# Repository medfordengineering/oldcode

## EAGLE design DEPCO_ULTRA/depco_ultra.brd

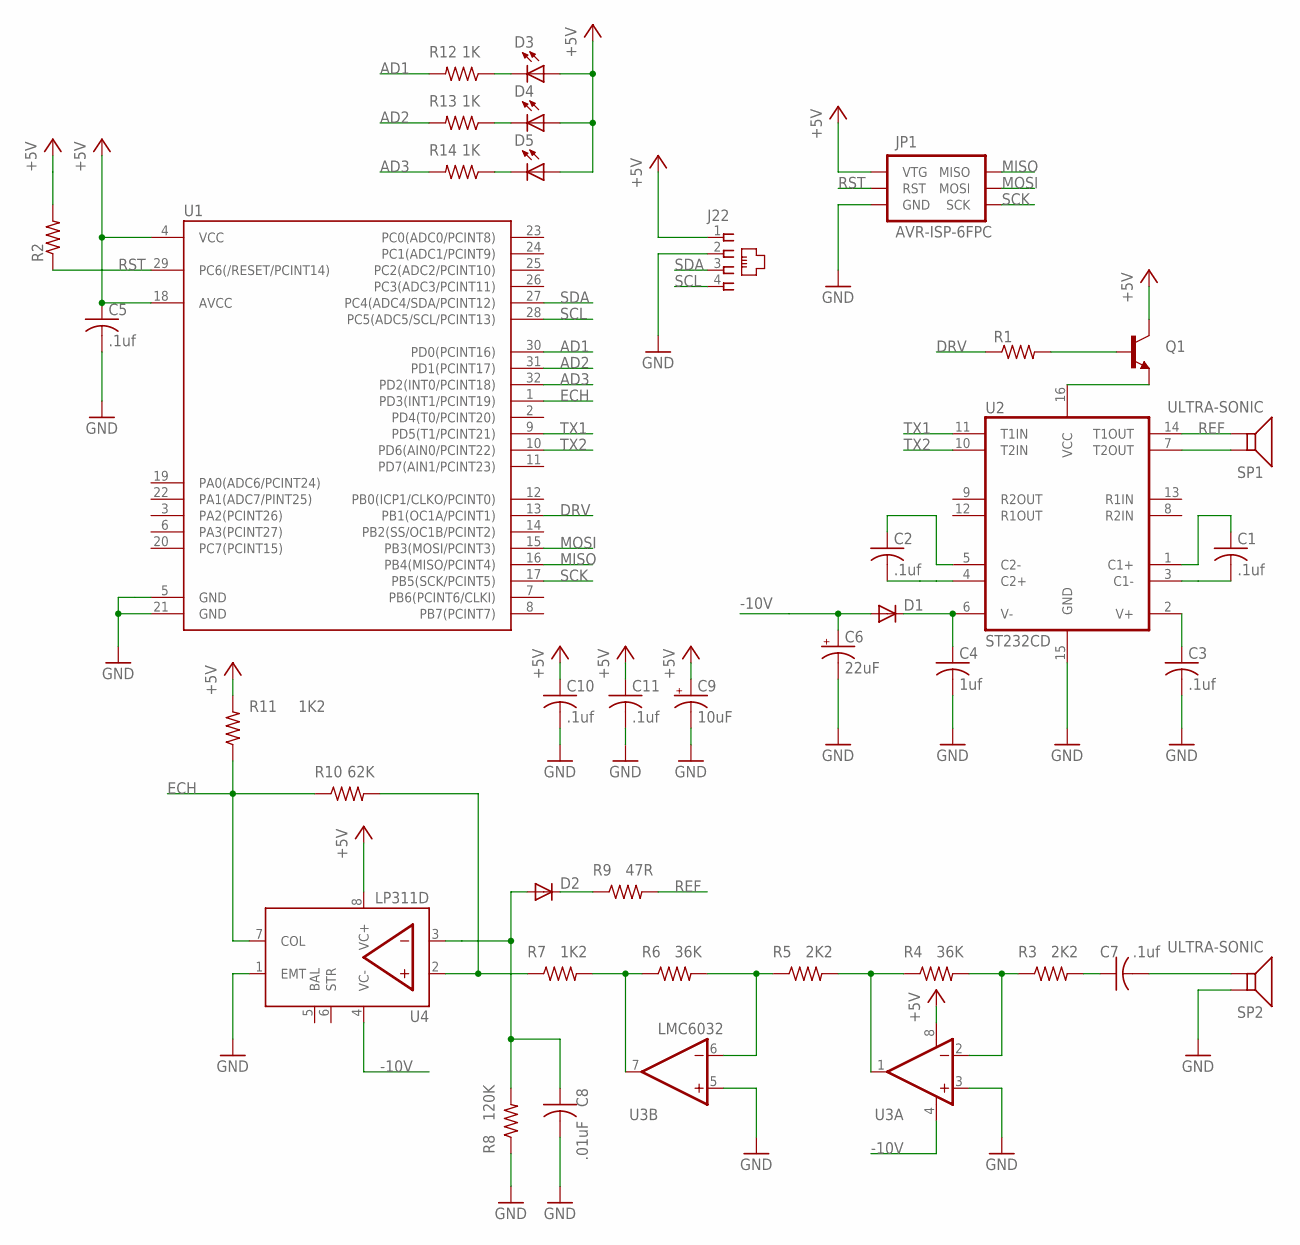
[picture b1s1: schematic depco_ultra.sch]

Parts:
C1, C2, C3, C5, C7, C10, C11: .1uf; C0805
C4: 1uf; C0805
C6: 22uF; PANASONIC_D
C8: .01uF; C0805
C9: 10uF; PANASONIC_D
D1, D2: DIODESOD; SOD-323
D3, D4, D5: LED_MS; LED-0805
J22: 555165-2
JP1: AVR-ISP-6FPC; 84981-6
Q1: TRANSISTOR_NPNSOT23; SOT23
R1, R2: R-US_M0805; M0805
R3, R5: 2K2; M0805
R4, R6: 36K; M0805
R7, R11: 1K2; M0805
R8: 120K; M0805
R9: 47R; M0805
R10: 62K; M0805
R12, R13, R14: 1K; M0805
SP1, SP2: ULTRA-SONIC; 400_D64INC
U1: ATTINY48-QFN; TQFP32-08
U2: ST232CD; SO016
U3: LMC6032; SO08
U4: LP311D; SO08

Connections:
+5V: C5.1, C9.+, C10.1, C11.1, D3.A, D4.A, D5.A, J22.1, JP1.5 (VTG), Q1.3 (C), R2.2, R11.2, U1.4 (VCC), U1.18 (AVCC), U3.8 (V+), U4.8 (VC+)
-10V: C6.+, D1.2 (A), U3.4 (V-), U4.4 (VC-)
AD1: R12.2, U1.30 (PD0(PCINT16))
AD2: R13.2, U1.31 (PD1(PCINT17))
AD3: R14.2, U1.32 (PD2(INT0/PCINT18))
DRV: R1.1, U1.13 (PB1(OC1A/PCINT1))
ECH: R10.1, R11.1, U1.1 (PD3(INT1/PCINT19)), U4.7 (COL)
GND: C3.2, C4.2, C5.2, C6.-, C8.2, C9.-, C10.2, C11.2, J22.2, JP1.6 (GND), R8.1, SP2.1 (P+), U1.5 (GND), U1.21 (GND), U2.15 (GND), U3.3 (+IN), U3.5 (+IN), U4.1 (EMT)
MISO: JP1.2 (MISO), U1.16 (PB4(MISO/PCINT4))
MOSI: JP1.3 (MOSI), U1.15 (PB3(MOSI/PCINT3))
unnamed: C2.1, U2.5 (C2-)
unnamed: C2.2, U2.4 (C2+)
unnamed: C1.1, U2.1 (C1+)
unnamed: C1.2, U2.3 (C1-)
unnamed: C4.1, D1.1 (C), U2.6 (V-)
unnamed: C3.1, U2.2 (V+)
unnamed: Q1.2 (E), U2.16 (VCC)
unnamed: Q1.1 (B), R1.2
unnamed: D3.C, R12.1
unnamed: R5.1, R6.2, U3.6 (-IN)
unnamed: C7.1, R3.2
unnamed: R4.1, R5.2, U3.1 (OUT)
unnamed: R3.1, R4.2, U3.2 (-IN)
unnamed: R6.1, R7.2, U3.7 (OUT)
unnamed: R7.1, R10.2, U4.2 (+IN)
unnamed: SP1.1 (P+), U2.7 (T2OUT)
unnamed: C7.2, SP2.2 (P-)
unnamed: C8.1, D2.2 (A), R8.2, U4.3 (-IN)
unnamed: D4.C, R13.1
unnamed: D5.C, R14.1
unnamed: D2.1 (C), R9.1
PA3(PCINT27): U1.6 (PA3(PCINT27))
PC7(PCINT15): U1.20 (PC7(PCINT15))
REF: R9.2, SP1.2 (P-), U2.14 (T1OUT)
RST: JP1.4 (RST), R2.1, U1.29 (PC6(/RESET/PCINT14))
SCK: JP1.1 (SCK), U1.17 (PB5(SCK/PCINT5))
SCL: J22.4, U1.28 (PC5(ADC5/SCL/PCINT13))
SDA: J22.3, U1.27 (PC4(ADC4/SDA/PCINT12))
TX1: U1.9 (PD5(T1/PCINT21)), U2.11 (T1IN)
TX2: U1.10 (PD6(AIN0/PCINT22)), U2.10 (T2IN)

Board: 2 copper layers, 39 parts (33 on the bottom side), 38 nets, no tracks yet.

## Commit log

2016-02-15 first new all
2016-02-15 dep and mot
2017-04-26 added test file

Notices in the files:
parts and their libraries:
SparkFun2: Licensing: CC v3.0 Share-Alike You are welcome to use this library for commercial purposes.
